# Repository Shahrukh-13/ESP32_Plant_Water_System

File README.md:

# ESP32_Plant_Water_System
ESP32 Plant Water System Project

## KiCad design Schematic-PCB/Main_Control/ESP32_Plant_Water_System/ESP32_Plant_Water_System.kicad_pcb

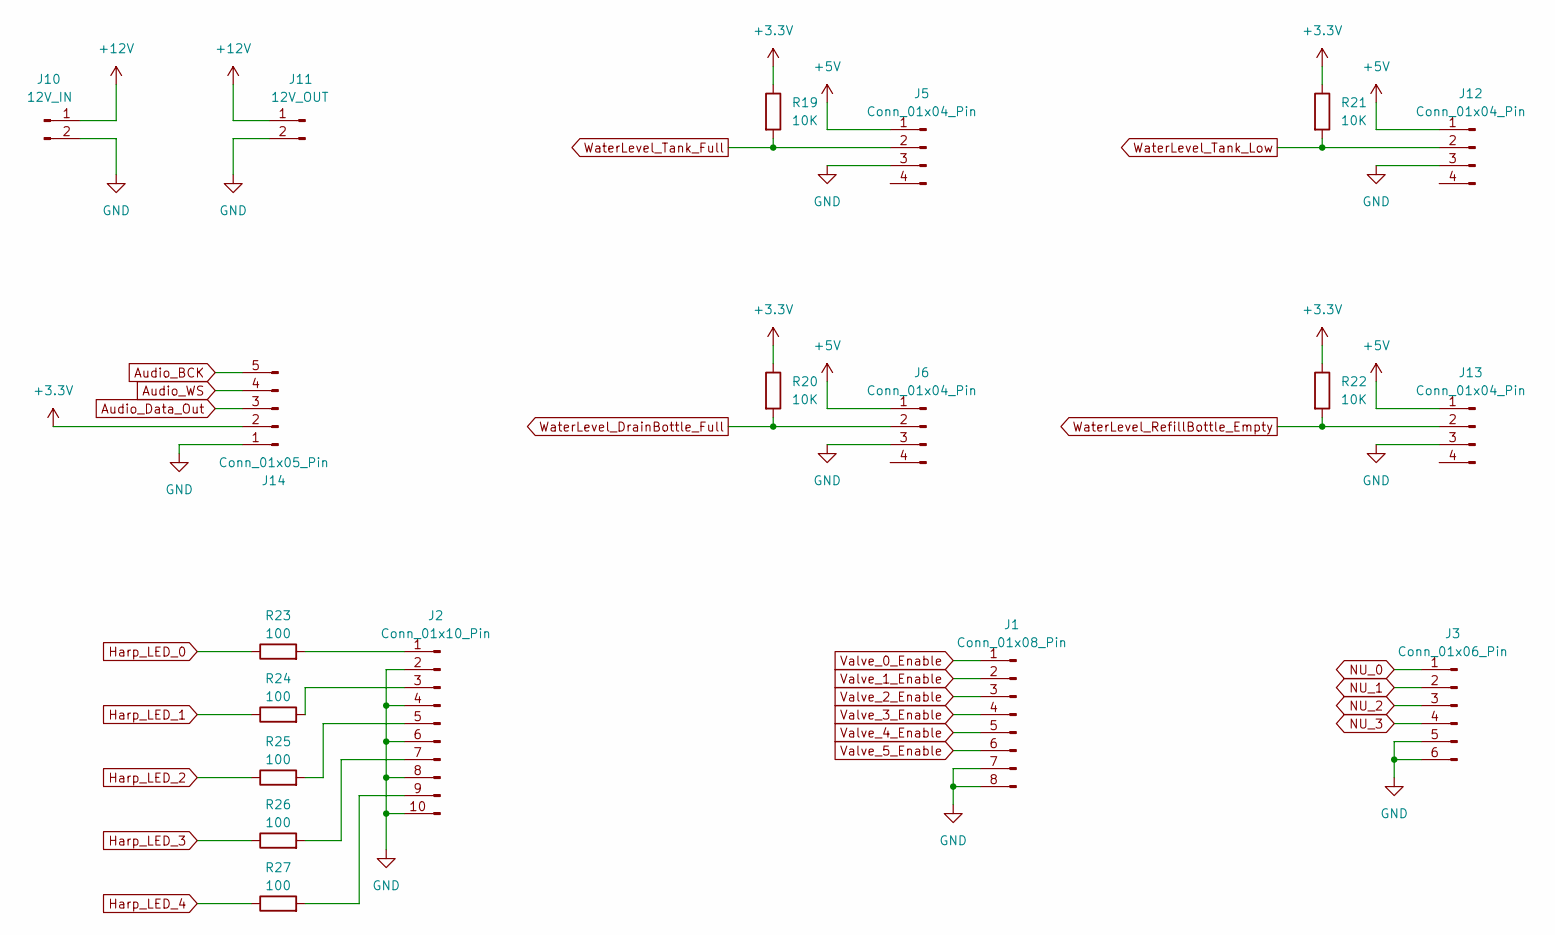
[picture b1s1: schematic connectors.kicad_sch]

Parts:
J1: Conn_01x08_Pin; JST_XH_B8B-XH-A_1x08_P2.50mm_Vertical
J2: Conn_01x10_Pin; JST_XH_B10B-XH-A_1x10_P2.50mm_Vertical
J3: Conn_01x06_Pin; JST_XH_B6B-XH-A_1x06_P2.50mm_Vertical
J5, J6, J12, J13: Conn_01x04_Pin; JST_XH_B4B-XH-A_1x04_P2.50mm_Vertical
J10: 12V_IN; Altech_AK100_1x02_P5.00mm
J11: 12V_OUT; Altech_AK100_1x02_P5.00mm
J14: Conn_01x05_Pin; JST_PH_B5B-PH-K_1x05_P2.00mm_Vertical
R19, R20, R21, R22: 10K; R_Axial_DIN0207_L6.3mm_D2.5mm_P10.16mm_Horizontal
R23, R24, R25, R26, R27: 100; R_Axial_DIN0207_L6.3mm_D2.5mm_P10.16mm_Horizontal

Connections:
+3.3V: J14.2, R19.1, R20.1, R21.1, R22.1; also elsewhere on the board
+5V: J5.1, J6.1, J12.1, J13.1; also elsewhere on the board
+12V: J10.1, J11.1; also elsewhere on the board
Audio_BCK: J14.5; also elsewhere on the board
Audio_Data_Out: J14.3; also elsewhere on the board
Audio_WS: J14.4; also elsewhere on the board
GND: J1.7, J1.8, J2.2, J2.4, J2.6, J2.8, J2.10, J3.5, J3.6, J5.3, J6.3, J10.2, J11.2, J12.3, J13.3, J14.1; also elsewhere on the board
Harp_LED_0: R23.1; also elsewhere on the board
Harp_LED_1: R24.1; also elsewhere on the board
Harp_LED_2: R25.1; also elsewhere on the board
Harp_LED_3: R26.1; also elsewhere on the board
Harp_LED_4: R27.1; also elsewhere on the board
NU_0: J3.1; also elsewhere on the board
NU_1: J3.2; also elsewhere on the board
NU_2: J3.3; also elsewhere on the board
NU_3: J3.4; also elsewhere on the board
unnamed: J2.1, R23.2
unnamed: J2.3, R24.2
unnamed: J2.5, R25.2
unnamed: J2.7, R26.2
unnamed: J2.9, R27.2
Valve_0_Enable: J1.1; also elsewhere on the board
Valve_1_Enable: J1.2; also elsewhere on the board
Valve_2_Enable: J1.3; also elsewhere on the board
Valve_3_Enable: J1.4; also elsewhere on the board
Valve_4_Enable: J1.5; also elsewhere on the board
Valve_5_Enable: J1.6; also elsewhere on the board
WaterLevel_DrainBottle_Full: J6.2, R20.2; also elsewhere on the board
WaterLevel_RefillBottle_Empty: J13.2, R22.2; also elsewhere on the board
WaterLevel_Tank_Full: J5.2, R19.2; also elsewhere on the board
WaterLevel_Tank_Low: J12.2, R21.2; also elsewhere on the board

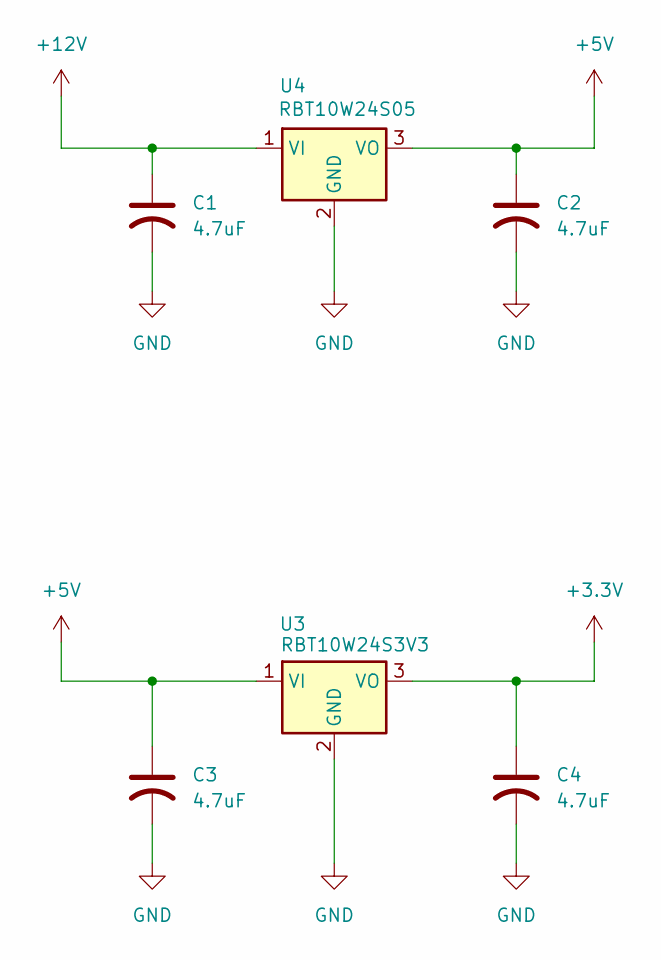
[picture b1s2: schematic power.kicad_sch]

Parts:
C1, C2, C3, C4: 4.7uF; CP_Radial_D5.0mm_P2.50mm
U3: RBT10W24S3V3; SIP3_11.6x8.5mm
U4: RBT10W24S05; SIP3_11.6x8.5mm

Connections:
+3.3V: C4.1, U3.3 (VO); also elsewhere on the board
+5V: C2.1, C3.1, U3.1 (VI), U4.3 (VO); also elsewhere on the board
+12V: C1.1, U4.1 (VI); also elsewhere on the board
GND: C1.2, C2.2, C3.2, C4.2, U3.2 (GND), U4.2 (GND); also elsewhere on the board

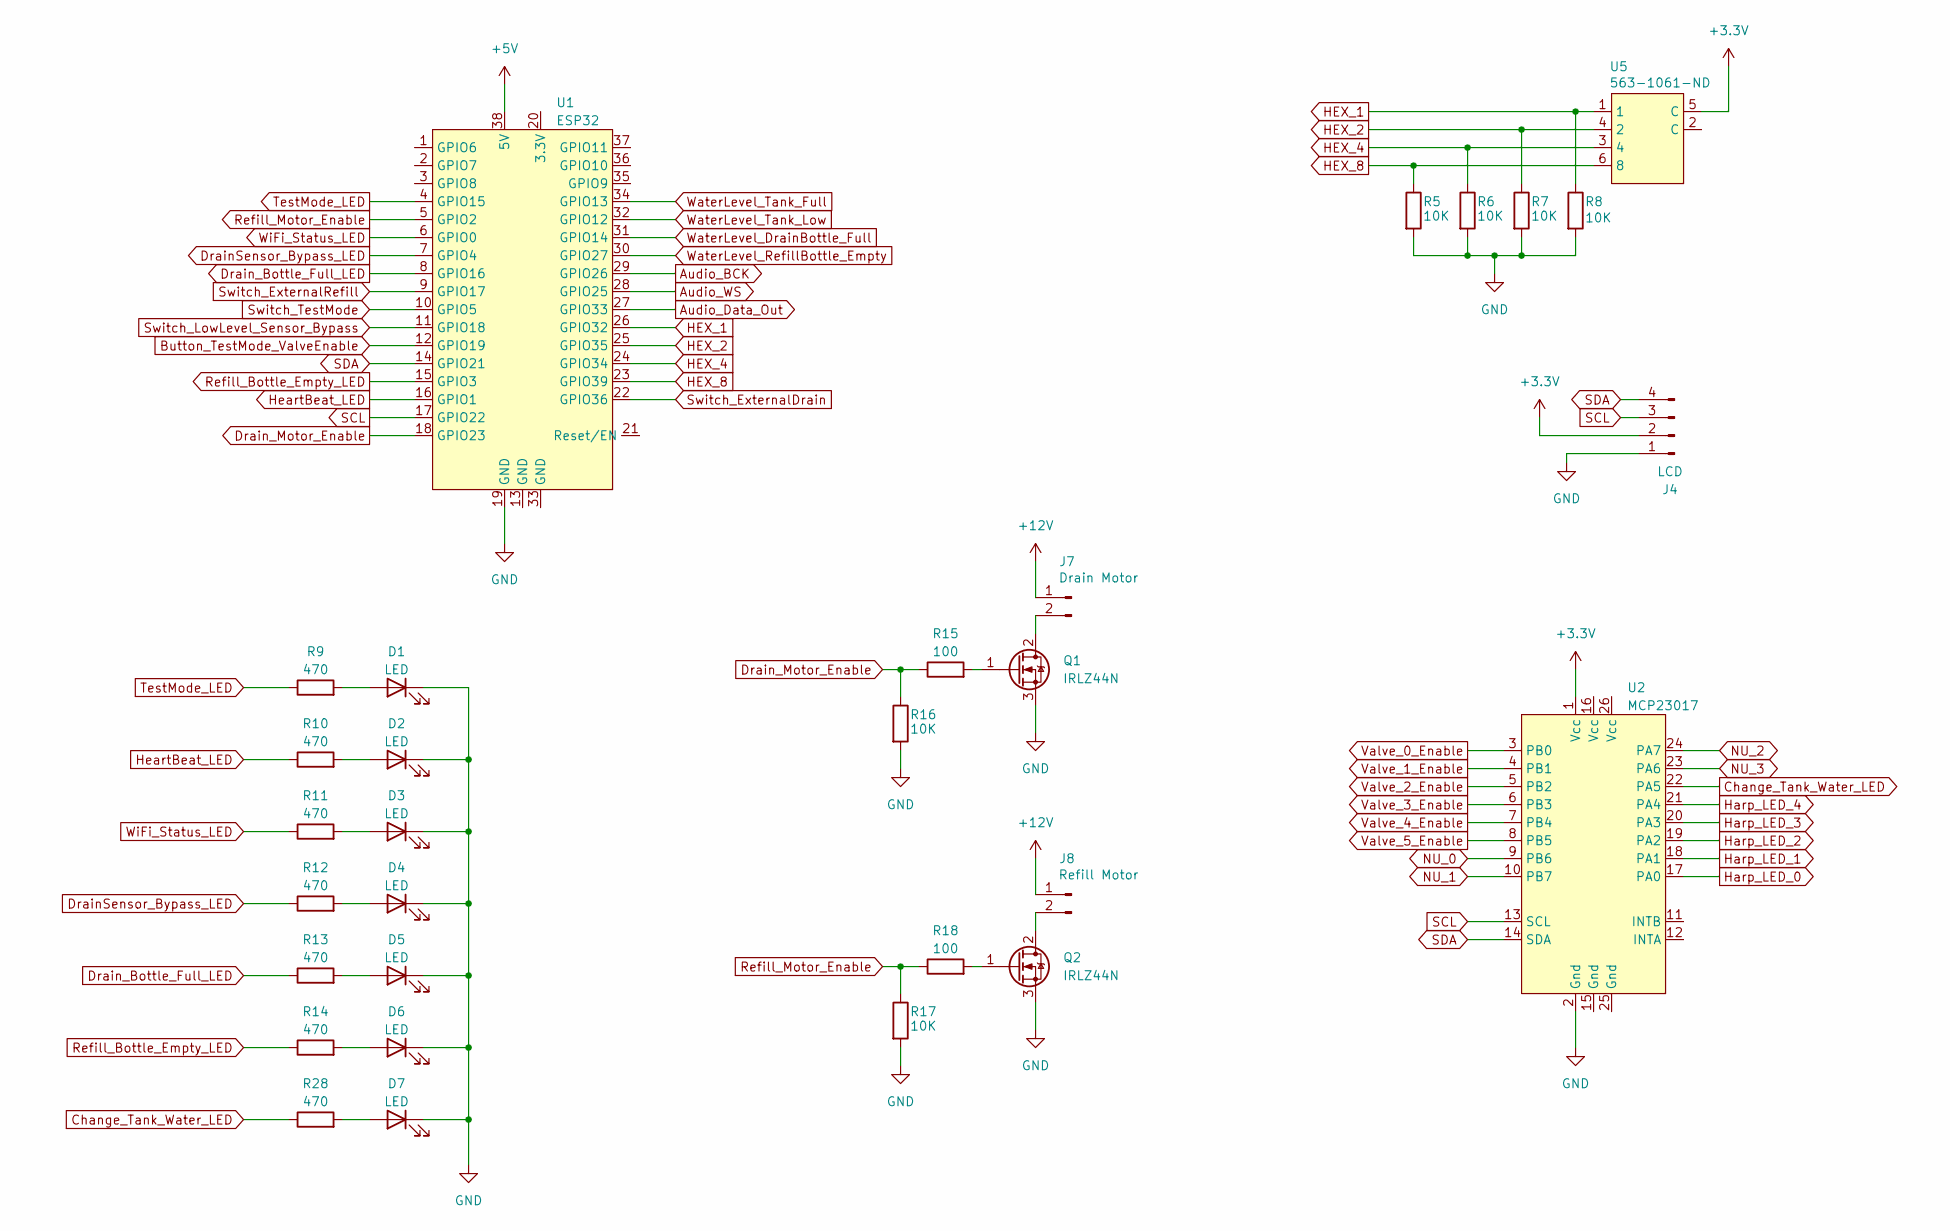
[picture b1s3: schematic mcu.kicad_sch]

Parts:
D1, D2, D3, D4, D5, D6, D7: LED; LED_D5.0mm
J4: LCD; PinHeader_1x04_P2.54mm_Vertical
J7: Drain Motor; JST_XH_B2B-XH-A_1x02_P2.50mm_Vertical
J8: Refill Motor; JST_XH_B2B-XH-A_1x02_P2.50mm_Vertical
Q1, Q2: IRLZ44N; TO-220-3_Vertical
R5, R6, R7, R8, R16, R17: 10K; R_Axial_DIN0207_L6.3mm_D2.5mm_P10.16mm_Horizontal
R9, R10, R11, R12, R13, R14, R28: 470; R_Axial_DIN0207_L6.3mm_D2.5mm_P10.16mm_Horizontal
R15, R18: 100; R_Axial_DIN0207_L6.3mm_D2.5mm_P10.16mm_Horizontal
U1: ESP32; ESP32D-USBC
U2: MCP23017; MCP23017_Module
U5: 563-1061-ND

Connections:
+3.3V: J4.2, U2.1 (Vcc), U5.5 (C); also elsewhere on the board
+5V: U1.38 (5V); also elsewhere on the board
+12V: J7.1, J8.1; also elsewhere on the board
Audio_BCK: U1.29 (GPIO26); also elsewhere on the board
Audio_Data_Out: U1.27 (GPIO33); also elsewhere on the board
Audio_WS: U1.28 (GPIO25); also elsewhere on the board
Button_TestMode_ValveEnable: U1.12 (GPIO19); also elsewhere on the board
Change_Tank_Water_LED: R28.1, U2.22 (PA5)
DrainSensor_Bypass_LED: R12.1, U1.7 (GPIO4)
Drain_Bottle_Full_LED: R13.1, U1.8 (GPIO16)
Drain_Motor_Enable: R15.1, R16.1, U1.18 (GPIO23)
GND: D1.1 (K), D2.1 (K), D3.1 (K), D4.1 (K), D5.1 (K), D6.1 (K), D7.1 (K), J4.1, Q1.3 (S), Q2.3 (S), R5.2, R6.2, R7.2, R8.2, R16.2, R17.2, U1.19 (GND), U2.2 (Gnd); also elsewhere on the board
HEX_1: R8.1, U1.26 (GPIO32), U5.1
HEX_2: R7.1, U1.25 (GPIO35), U5.4 (2)
HEX_4: R6.1, U1.24 (GPIO34), U5.3 (4)
HEX_8: R5.1, U1.23 (GPIO39), U5.6 (8)
Harp_LED_0: U2.17 (PA0); also elsewhere on the board
Harp_LED_1: U2.18 (PA1); also elsewhere on the board
Harp_LED_2: U2.19 (PA2); also elsewhere on the board
Harp_LED_3: U2.20 (PA3); also elsewhere on the board
Harp_LED_4: U2.21 (PA4); also elsewhere on the board
HeartBeat_LED: R10.1, U1.16 (GPIO1)
NU_0: U2.9 (PB6); also elsewhere on the board
NU_1: U2.10 (PB7); also elsewhere on the board
NU_2: U2.24 (PA7); also elsewhere on the board
NU_3: U2.23 (PA6); also elsewhere on the board
unnamed: D1.2 (A), R9.2
unnamed: D2.2 (A), R10.2
unnamed: D3.2 (A), R11.2
unnamed: D4.2 (A), R12.2
unnamed: D5.2 (A), R13.2
unnamed: D6.2 (A), R14.2
unnamed: D7.2 (A), R28.2
unnamed: J7.2, Q1.2 (D)
unnamed: J8.2, Q2.2 (D)
unnamed: Q1.1 (G), R15.2
unnamed: Q2.1 (G), R18.2
Refill_Bottle_Empty_LED: R14.1, U1.15 (GPIO3)
Refill_Motor_Enable: R17.1, R18.1, U1.5 (GPIO2)
SCL: J4.3, U1.17 (GPIO22), U2.13 (SCL)
SDA: J4.4, U1.14 (GPIO21), U2.14 (SDA)
Switch_ExternalDrain: U1.22 (GPIO36); also elsewhere on the board
Switch_ExternalRefill: U1.9 (GPIO17); also elsewhere on the board
Switch_LowLevel_Sensor_Bypass: U1.11 (GPIO18); also elsewhere on the board
Switch_TestMode: U1.10 (GPIO5); also elsewhere on the board
TestMode_LED: R9.1, U1.4 (GPIO15)
Valve_0_Enable: U2.3 (PB0); also elsewhere on the board
Valve_1_Enable: U2.4 (PB1); also elsewhere on the board
Valve_2_Enable: U2.5 (PB2); also elsewhere on the board
Valve_3_Enable: U2.6 (PB3); also elsewhere on the board
Valve_4_Enable: U2.7 (PB4); also elsewhere on the board
Valve_5_Enable: U2.8 (PB5); also elsewhere on the board
WaterLevel_DrainBottle_Full: U1.31 (GPIO14); also elsewhere on the board
WaterLevel_RefillBottle_Empty: U1.30 (GPIO27); also elsewhere on the board
WaterLevel_Tank_Full: U1.34 (GPIO13); also elsewhere on the board
WaterLevel_Tank_Low: U1.32 (GPIO12); also elsewhere on the board
WiFi_Status_LED: R11.1, U1.6 (GPIO0)

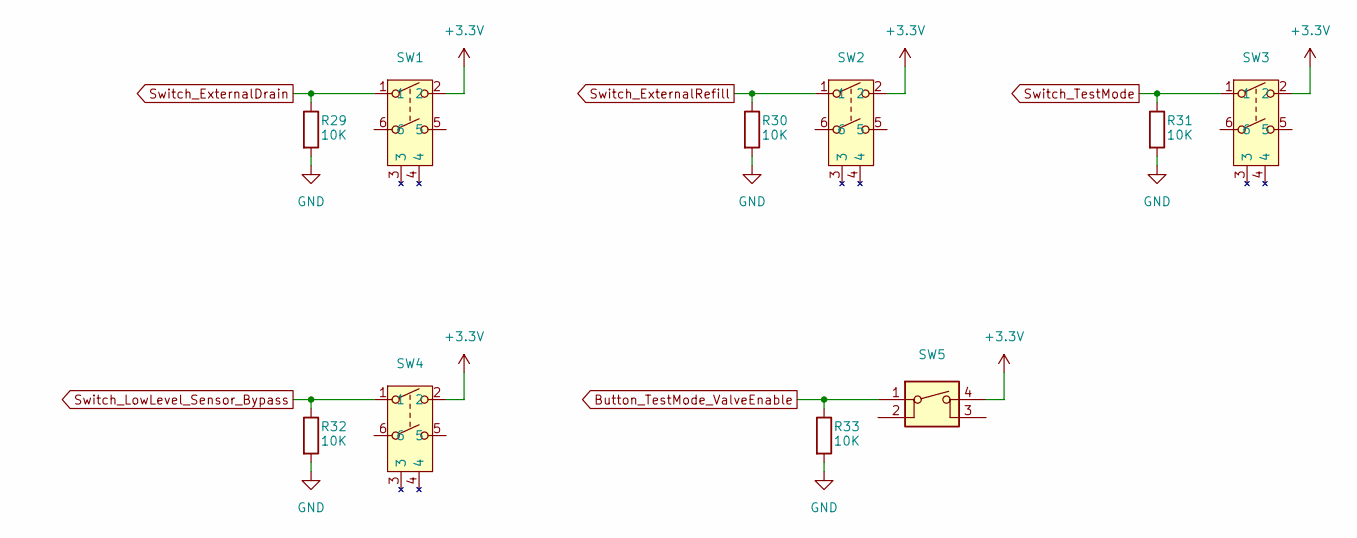
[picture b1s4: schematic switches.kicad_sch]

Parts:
R29, R30, R31, R32, R33: 10K; R_Axial_DIN0207_L6.3mm_D2.5mm_P10.16mm_Horizontal
SW1, SW2, SW3, SW4: SW_DPST_6Pin
SW5: SW_SPST_4Pin

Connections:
+3.3V: SW1.2, SW2.2, SW3.2, SW4.2, SW5.4; also elsewhere on the board
Button_TestMode_ValveEnable: R33.1, SW5.1; also elsewhere on the board
GND: R29.2, R30.2, R31.2, R32.2, R33.2; also elsewhere on the board
Switch_ExternalDrain: R29.1, SW1.1; also elsewhere on the board
Switch_ExternalRefill: R30.1, SW2.1; also elsewhere on the board
Switch_LowLevel_Sensor_Bypass: R32.1, SW4.1; also elsewhere on the board
Switch_TestMode: R31.1, SW3.1; also elsewhere on the board

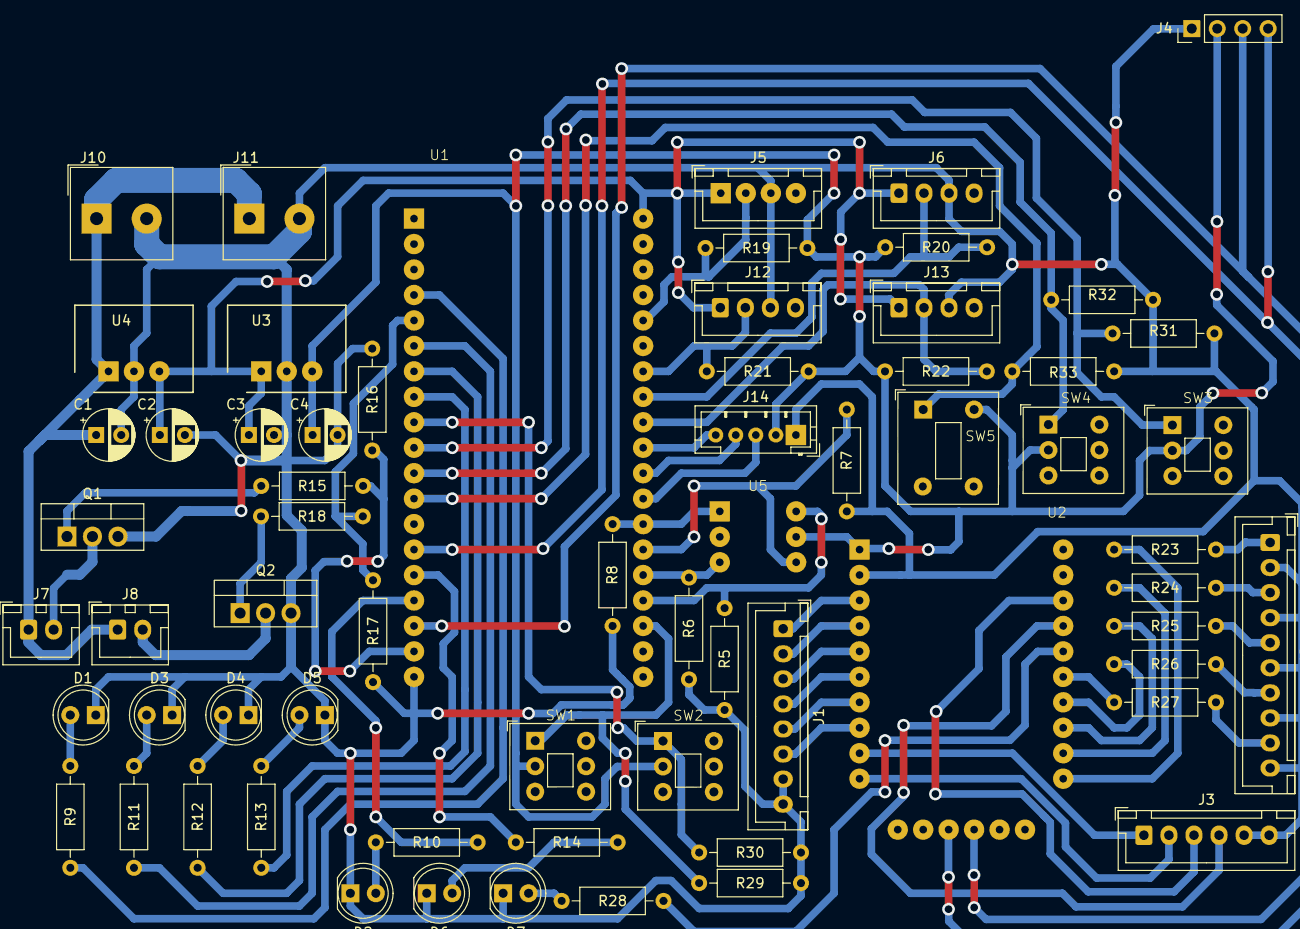
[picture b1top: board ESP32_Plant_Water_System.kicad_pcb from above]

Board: 2 copper layers, 65 parts (0 on the bottom side), 62 nets.

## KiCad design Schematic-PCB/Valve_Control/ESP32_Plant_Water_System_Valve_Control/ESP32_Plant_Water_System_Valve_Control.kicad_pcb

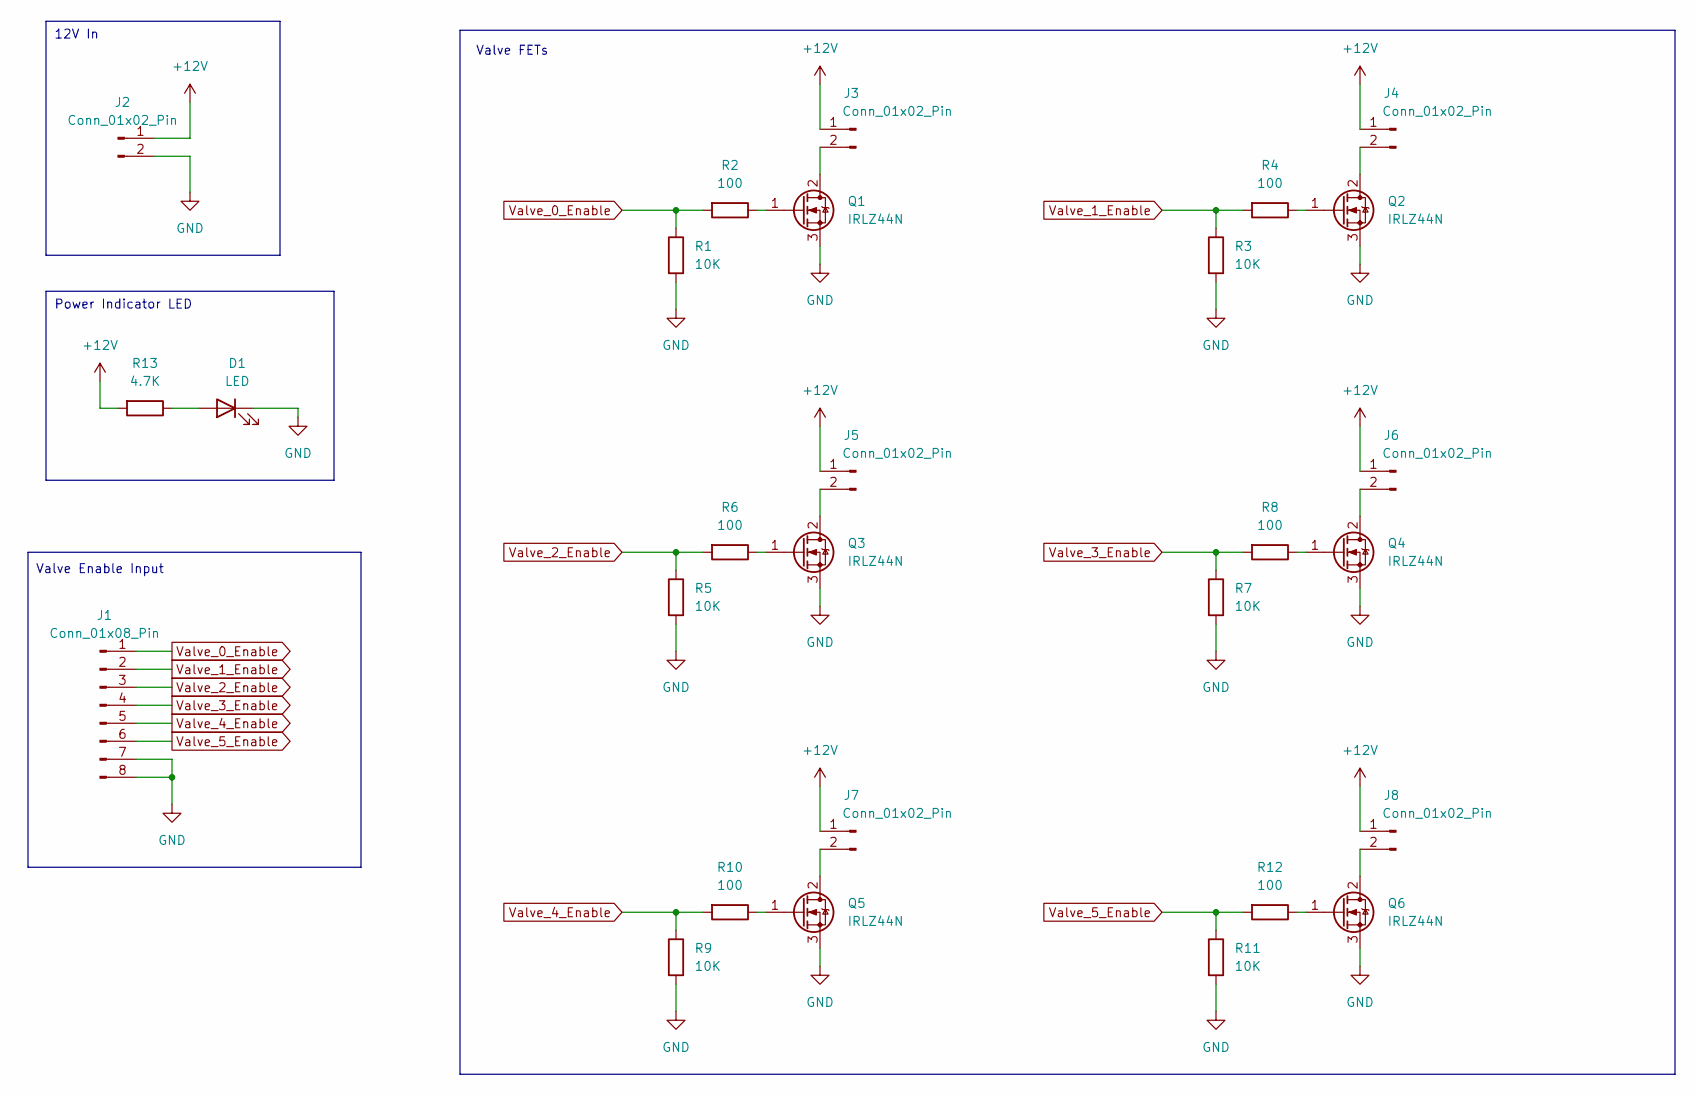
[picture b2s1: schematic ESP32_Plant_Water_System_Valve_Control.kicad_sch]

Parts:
D1: LED; LED_D5.0mm
J1: Conn_01x08_Pin; JST_XH_B8B-XH-A_1x08_P2.50mm_Vertical
J2: Conn_01x02_Pin; Altech_AK100_1x02_P5.00mm
J3, J4, J5, J6, J7, J8: Conn_01x02_Pin; JST_XH_B2B-XH-A_1x02_P2.50mm_Vertical
Q1, Q2, Q3, Q4, Q5, Q6: IRLZ44N; TO-220-3_Vertical
R1, R3, R5, R7, R9, R11: 10K; R_Axial_DIN0207_L6.3mm_D2.5mm_P10.16mm_Horizontal
R2, R4, R6, R8, R10, R12: 100; R_Axial_DIN0207_L6.3mm_D2.5mm_P10.16mm_Horizontal
R13: 4.7K; R_Axial_DIN0207_L6.3mm_D2.5mm_P10.16mm_Horizontal

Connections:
+12V: J2.1, J3.1, J4.1, J5.1, J6.1, J7.1, J8.1, R13.2
GND: D1.1 (K), J1.7, J1.8, J2.2, Q1.3 (S), Q2.3 (S), Q3.3 (S), Q4.3 (S), Q5.3 (S), Q6.3 (S), R1.2, R3.2, R5.2, R7.2, R9.2, R11.2
unnamed: D1.2 (A), R13.1
unnamed: J3.2, Q1.2 (D)
unnamed: J4.2, Q2.2 (D)
unnamed: J5.2, Q3.2 (D)
unnamed: J6.2, Q4.2 (D)
unnamed: J7.2, Q5.2 (D)
unnamed: J8.2, Q6.2 (D)
unnamed: Q1.1 (G), R2.1
unnamed: Q2.1 (G), R4.1
unnamed: Q3.1 (G), R6.1
unnamed: Q4.1 (G), R8.1
unnamed: Q5.1 (G), R10.1
unnamed: Q6.1 (G), R12.1
Valve_0_Enable: J1.1, R1.1, R2.2
Valve_1_Enable: J1.2, R3.1, R4.2
Valve_2_Enable: J1.3, R5.1, R6.2
Valve_3_Enable: J1.4, R7.1, R8.2
Valve_4_Enable: J1.5, R9.1, R10.2
Valve_5_Enable: J1.6, R11.1, R12.2

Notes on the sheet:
Power Indicator LED
Valve FETs
12V In
Valve Enable Input

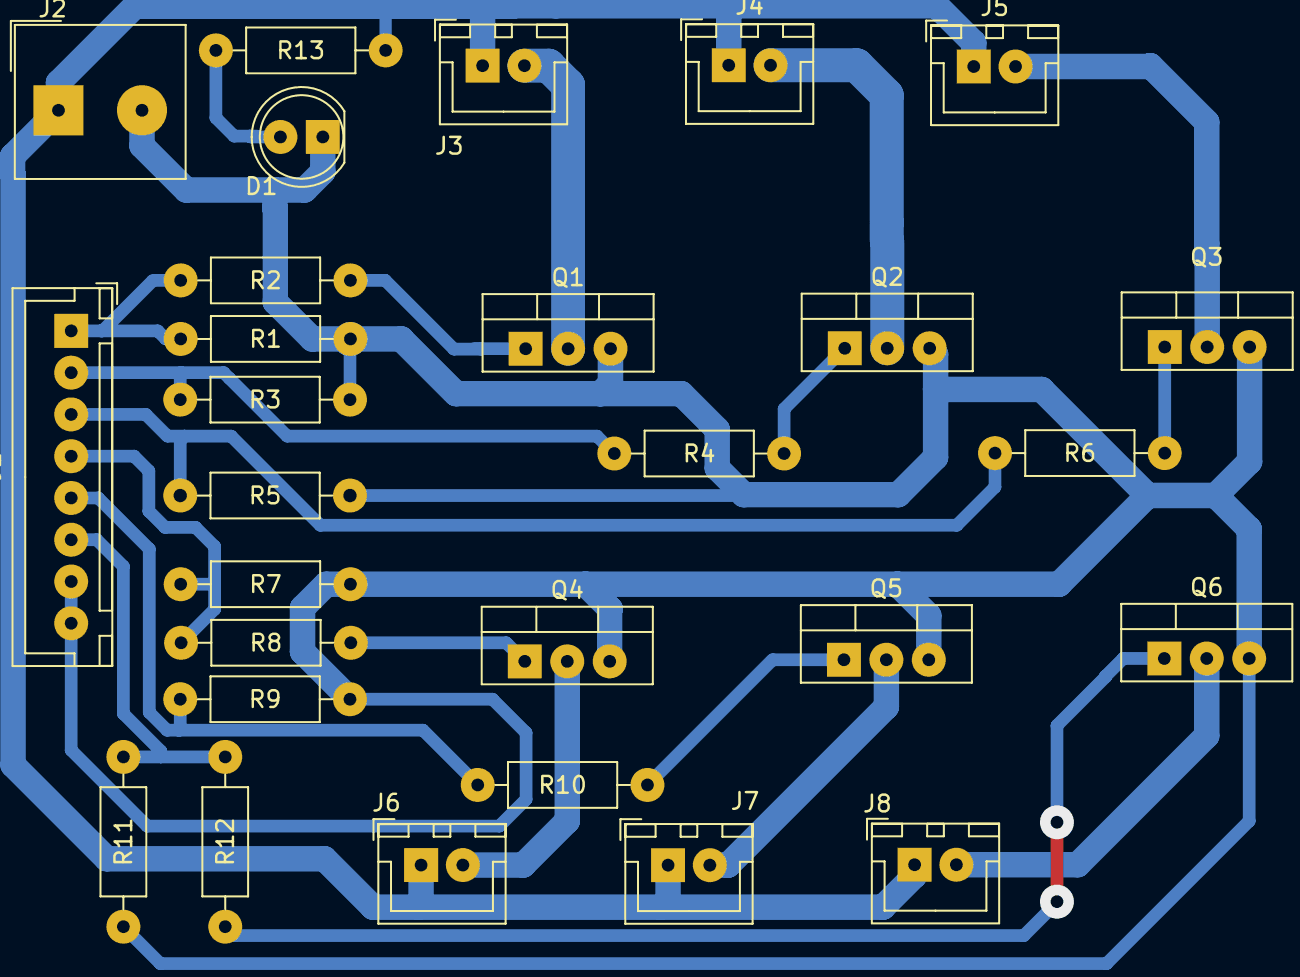
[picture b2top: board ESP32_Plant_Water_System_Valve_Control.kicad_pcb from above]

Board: 2 copper layers, 28 parts (0 on the bottom side), 21 nets.

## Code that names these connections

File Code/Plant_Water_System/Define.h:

#ifndef DEFINE_H
#define DEFINE_H

#include "WiFi.h"
#include <AsyncTCP.h>
#include <ESPAsyncWebServer.h>
#include <Wire.h>
#include <Adafruit_MCP23X17.h>
#include <EEPROM.h>
#include "time.h"

//#define SERIAL_DEBUG

//ESP32 Digital IO
#define WiFi_Status_LED                 0
#define HeartBeat_LED                   1
#define Refill_Motor_Enable             2
#define Refill_Bottle_Empty_LED         3
#define DrainSensor_Bypass_LED          4
#define Switch_TestMode                 5
#define WaterLevel_Tank_Low             12
#define WaterLevel_Tank_Full            13
#define WaterLevel_DrainBottle_Full     14
#define TestMode_LED                    15
#define Drain_Bottle_Full_LED           16
#define Switch_ExternalRefill           17
#define Switch_LowLevel_Sensor_Bypass   18
#define Button_TestMode_ValveEnable     19
#define Drain_Motor_Enable              23
#define WaterLevel_RefillBottle_Empty   27
#define HEX_1                           32
#define HEX_4                           34
#define HEX_2                           35
#define Switch_ExternalDrain            36
#define HEX_8                           39

//ESP32 I2S Audio
#define Audio_BCK                       26
#define Audio_WS                        25
#define Audio_Data_Out                  33



//MCP A
#define Harp_LED_0                      0
#define Harp_LED_1                      1
#define Harp_LED_2                      2
#define Harp_LED_3                      3
#define Harp_LED_4                      4
#define Change_Tank_Water_LED           5
#define NU_3                            6
#define NU_2                            7
//MCP B
#define Valve_0_Enable                  8
#define Valve_1_Enable                  9
#define Valve_2_Enable                  10
#define Valve_3_Enable                  11
#define Valve_4_Enable                  12
#define Valve_5_Enable                  13          
#define NU_0                            14
#define NU_1                            15


//EEPROM
#define EEPROM_SSID_ADDRESS                   0   
#define EEPROM_PASSWORD_ADDRESS               50  
#define EEPROM_PLANT1_TIME_ADDRESS            100
#define EEPROM_PLANT2_TIME_ADDRESS            150
#define EEPROM_PLANT3_TIME_ADDRESS            200
#define EEPROM_PLANT4_TIME_ADDRESS            250
#define EEPROM_PLANT5_TIME_ADDRESS            300
#define EEPROM_POWERCYCLE_COUNT_ADDRESS       350
#define EEPROM_PLANT1_VALVE_OPEN_SEC          351
#define EEPROM_PLANT2_VALVE_OPEN_SEC          352
#define EEPROM_PLANT3_VALVE_OPEN_SEC          353
#define EEPROM_PLANT4_VALVE_OPEN_SEC          354
#define EEPROM_PLANT5_VALVE_OPEN_SEC          355
#define EEPROM_AUDIO_MUTE_MIN                 356
#define EEPROM_WIFI_RECON_SEC                 357
#define EEPROM_WATER_CHANGE_INTERVAL_DAYS     358
#define EEPROM_WATER_CHANGE_DATE              359

//Declare the MCP23X17 object
Adafruit_MCP23X17 mcp;

//Declare the asynchronous web server object on port 80
AsyncWebServer server(80);


/******Typedefs****************************************/
typedef enum
{
  WATER_LEVEL_LOW = 0,
  WATER_LEVEL_NOT_FULL,
  WATER_LEVEL_FULL,
  WATER_LEVEL_INVALID
}water_level_state_t;

typedef enum
{
  MOTOR_DRAIN = 0,
  MOTOR_REFILL,
  MOTOR_MAX
}motor_id_t;

typedef enum
{
  MOTOR_STOP = 0,
  MOTOR_RUN,
}motor_state_t;

typedef enum
{
  APP_STATE_NORMAL = 0,
  APP_STATE_TEST,
}app_state_t;

typedef enum 
{
  VALVE0 = 0,
  VALVE1,
  VALVE2,
  VALVE3,
  VALVE4,
  VALVE5,
  VALVE_NONE,
  VALVE_MAX
}valve_id_t;
/*****************************************************/

/******Structures************************************/
struct water_level
{
  bool Sensor_Full_Val;
  bool Sensor_Low_Val;
  water_level_state_t State;
};

struct external_bottle_sensor
{
  bool Drain_Bottle_Full_Val;
  bool Refill_Bottle_Empty_Val;
};

struct motor_status
{
  bool Motor_Good_To_Run;
  bool Motor_Enable;
  bool Timed_Motor_Enable;
  bool Motor_Switch_val;
  motor_state_t State;
};

struct app_config
{
  app_state_t State;
  bool LowLevel_Sensor_Bypass_Val;
  bool Test_Mode_Switch_Val;
  bool HeartBeat_Toggle;
  bool Do_Harp_LED;
  bool Mute_Audio;
  uint8_t Hex_Encoder_Val;
  bool Test_Mode_Valve_Button_Val;
  bool Valve_Is_Open;
  uint8_t Which_Valve_Enabled;
  unsigned long CurrentMillis;
  unsigned long WiFi_Reconnect_Status_PreviousMillis;
  unsigned long Valve_Status_PreviousMillis;
  unsigned long Audio_Mute_Status_PreviousMillis;
  bool Change_water_Flag;
};

struct wifi_config
{
  uint8_t wifi_connection_timeout_count;
  uint8_t PowerCycle_Count;
  bool wifi_flag;
  String ssid_str;
  String password_str;
  String inputMessage; 
  char ssid[50];
  char password[50];
  String input;
};

struct ntp_time
{
  long gmtOffset_sec;
  int daylightOffset_sec;
  String Date;
  //String Year;
  String Time;
  char chDayOfMonth[3];                                    // Day of month (0 through 31).
  char chDayofWeek[4];                                     // Day of week (Sunday through Saturday).
  char chHour[3];                                          // Hour.
  char chMinute[3];                                        // Minute.
  char chMonth[4];                                         // Month.
  char* ntpServer;
  char chSecond[3];                                        // Second.
  char chYear[5];                                          // Year.
  char AM_PM[3];                                           // AM/PM.
};

struct webserver_info
{
  String   html;
  char     index_html[3000];
  String   Saved_WiFi_SSID;
  String   Saved_WiFi_Password; 
  String   New_WiFi_SSID;
  String   New_WiFi_Password; 
  String   Plant1_Time;
  String   Plant2_Time;
  String   Plant3_Time;
  String   Plant4_Time;
  String   Plant5_Time;
  uint16_t Plant1_Valve_Open_Sec;
  uint16_t Plant2_Valve_Open_Sec;
  uint16_t Plant3_Valve_Open_Sec;
  uint16_t Plant4_Valve_Open_Sec;
  uint16_t Plant5_Valve_Open_Sec;
  uint32_t Audio_Mute_Min;
  uint32_t WiFi_Reconnect_Sec;
  uint16_t Water_Change_Interval_days;
  String   Water_Change_Date;
};

struct time_valve_config
{
  valve_id_t  Valve_ID;
  String Vale_Time_String_Mon;
  String Vale_Time_String_Tue;
  String Vale_Time_String_Wed;
  String Vale_Time_String_Thu;
  String Vale_Time_String_Fri;
  String Vale_Time_String_Sat;
  String Vale_Time_String_Sun;
  uint16_t Valve_Open_Sec;
};
/****************************************************/

/*****Varriables*************************************/
struct water_level WL;
struct external_bottle_sensor EBS;
struct app_config AC;
struct motor_status MS[MOTOR_MAX];
struct wifi_config WC;
struct ntp_time NTP;
struct webserver_info WS;
struct time_valve_config TIME_VALVE_CFG[6];

String Default_WiFi_SSID = "Shahrukh13";
String Default_WiFi_Password = "password";
/****************************************************/
#endif // DEFINE_H
